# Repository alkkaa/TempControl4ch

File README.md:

# 4 Channel Temperature Control

## MAX31856 Precision Thermocouple to Digital Converter with Linearization

>### General Description
<p>
The MAX31856 performs cold-junction compensation and digitizes the signal from any type of thermocouple. 
The output data is formatted in degrees Celsius.<br>This converter resolves temperatures to 0.0078125°C, allows readings as high as +1800°C and as low as -210°C (depending on thermocouple type), and exhibits thermocouple voltage measurement accuracy of ±0.15%.
<br>The thermocouple inputs are protected against overvoltage conditions up to ±45V.<br>A lookup table (LUT) stores linearity correction data for several types of thermocouple (K, J, N, R, S, T, E, and B)
Line frequency filtering of 50Hz and 60Hz is included, as is thermocouple fault detection.<br>A SPI-compatible interface allows selection of thermocouple type and setup of the conversion and fault detection processes.
<p>

>### Benefits and Features
<ul>
    <li>Provides High-Accuracy Thermocouple Temperature Readings
        <ul>
        <li>Includes Automatic Linearization Correction for 8 Thermocouple Types</li>
        <li>±0.15% (max, -20°C to +85°C) Thermocouple Full-Scale and Linearity Error</li>
        <li>19-Bit, 0.0078125°C Thermocouple Temperature Resolution</li>
        </ul>
    </li>
    <li>Internal Cold-Junction Compensation Minimizes System Components
        <ul>
        <li>±0.7°C (max, -20°C to +85°C) Cold-Junction Accuracy </li>
        </ul>
    </li>
    <li>±45V Input Protection Provides Robust System Performance</li>
    <li>Simplifies System Fault Management and Troubleshooting
        <ul>
        <li>Detects Open Thermocouples</li>
        <li>Over- and Undertemperature Fault Detection</li>
        </ul>
    </li>
    <li>50Hz/60Hz Noise Rejection Filtering Improves System Performance
    </li>
    <li>14-Pin TSSOP Package
    </li>
</ul>

>### Images

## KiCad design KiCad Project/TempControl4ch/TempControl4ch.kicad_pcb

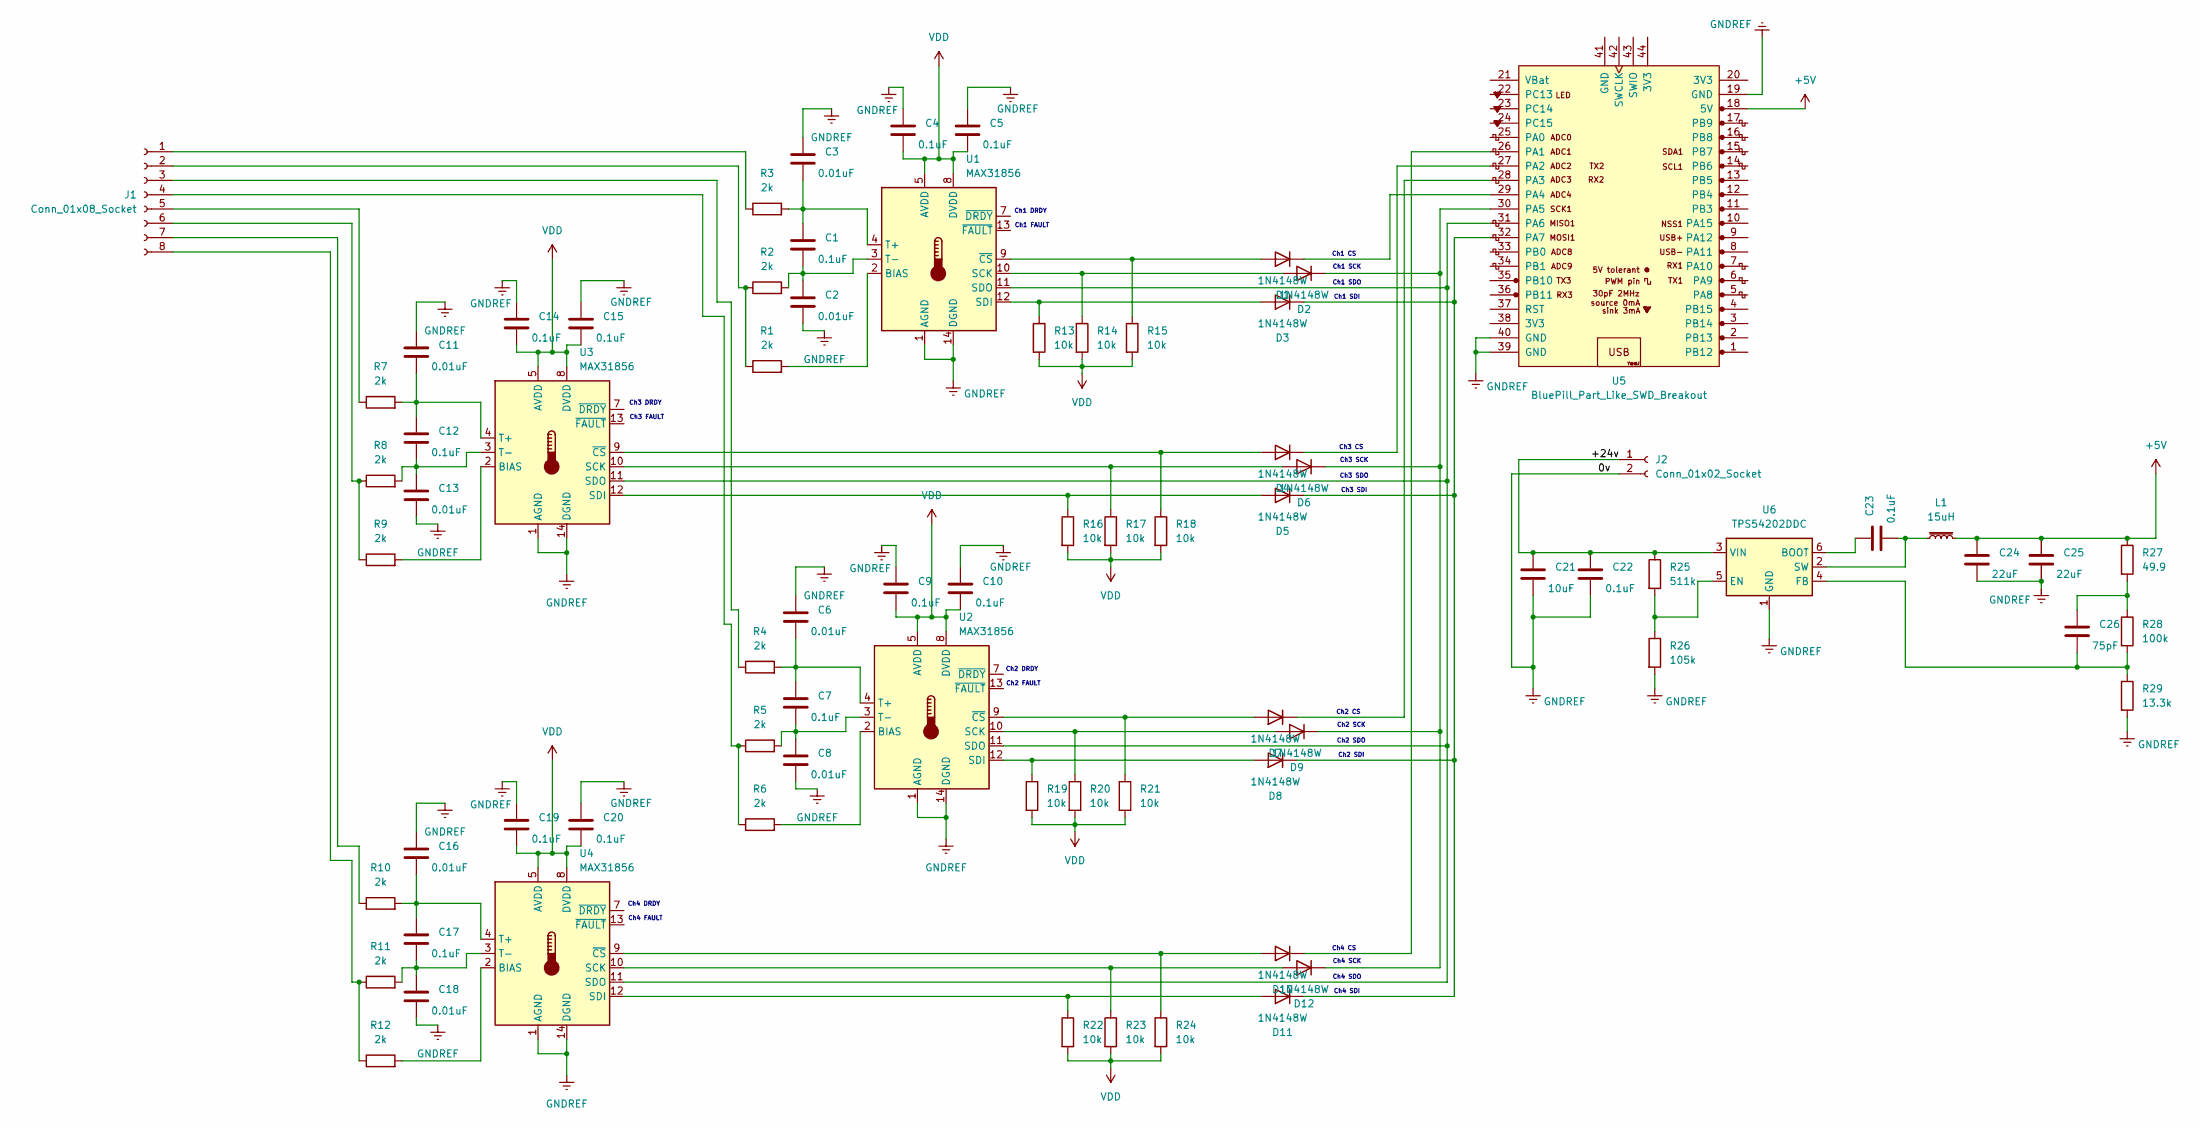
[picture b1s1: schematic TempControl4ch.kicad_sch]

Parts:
C1, C4, C5, C7, C9, C10, C12, C14, C15, C17, C19, C20, C22, C23: 0.1uF; C_1206_3216Metric_Pad1.33x1.80mm_HandSolder
C2, C3, C6, C8, C11, C13, C16, C18: 0.01uF; C_1206_3216Metric_Pad1.33x1.80mm_HandSolder
C21: 10uF; C_1206_3216Metric_Pad1.33x1.80mm_HandSolder
C24, C25: 22uF; C_1206_3216Metric_Pad1.33x1.80mm_HandSolder
C26: 75pF; C_1206_3216Metric_Pad1.33x1.80mm_HandSolder
D1, D2, D3, D4, D5, D6, D7, D8, D9, D10, D11, D12: 1N4148W; D_SOD-123
J1: Conn_01x08_Socket; PhoenixContact_MCV_1,5_8-G-3.81_1x08_P3.81mm_Vertical
J2: Conn_01x02_Socket; PhoenixContact_MCV_1,5_2-G-3.5_1x02_P3.50mm_Vertical
L1: 15uH; L_Sumida_CDMC6D28_7.25x6.5mm
R1, R2, R3, R4, R5, R6, R7, R8, R9, R10, R11, R12: 2k; R_1206_3216Metric_Pad1.30x1.75mm_HandSolder
R13, R14, R15, R16, R17, R18, R19, R20, R21, R22, R23, R24: 10k; R_1206_3216Metric_Pad1.30x1.75mm_HandSolder
R25: 511k; R_1206_3216Metric_Pad1.30x1.75mm_HandSolder
R26: 105k; R_1206_3216Metric_Pad1.30x1.75mm_HandSolder
R27: 49.9; R_1206_3216Metric_Pad1.30x1.75mm_HandSolder
R28: 100k; R_1206_3216Metric_Pad1.30x1.75mm_HandSolder
R29: 13.3k; R_1206_3216Metric_Pad1.30x1.75mm_HandSolder
U1, U2, U3, U4: MAX31856; TSSOP-14_4.4x5mm_P0.65mm
U5: BluePill_Part_Like_SWD_Breakout; BluePill_SWD_1
U6: TPS54202DDC; SOT-23-6

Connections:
+5V: C24.1, C25.1, L1.2, R27.1, U5.18 (5V)
/+24v: C21.1, C22.1, J2.1, R25.1, U6.3 (VIN)
GNDREF: C2.2, C3.1, C4.1, C5.1, C6.1, C8.2, C9.1, C10.1, C11.1, C13.2, C14.1, C15.1, C16.1, C18.2, C19.1, C20.1, C21.2, C22.2, C24.2, C25.2, J2.2, R26.2, R29.2, U1.1 (AGND), U1.14 (DGND), U2.1 (AGND), U2.14 (DGND), U3.1 (AGND), U3.14 (DGND), U4.1 (AGND), U4.14 (DGND), U5.19 (GND), U5.39 (GND), U5.40 (GND), U6.1 (GND)
unnamed: C26.1, R27.2, R28.1
unnamed: D1.2 (A), R15.1, U1.9 (~CS)
unnamed: D1.1 (K), U5.29 (PA4)
unnamed: D2.2 (A), R14.1, U1.10 (SCK)
unnamed: D3.2 (A), R13.1, U1.12 (SDI)
unnamed: D4.2 (A), R18.1, U3.9 (~CS)
unnamed: D4.1 (K), U5.27 (PA2)
unnamed: D5.2 (A), R16.1, U3.12 (SDI)
unnamed: D6.2 (A), R17.1, U3.10 (SCK)
unnamed: D7.2 (A), R21.1, U2.9 (~CS)
unnamed: D7.1 (K), U5.28 (PA3)
unnamed: D8.2 (A), R19.1, U2.12 (SDI)
unnamed: D9.2 (A), R20.1, U2.10 (SCK)
unnamed: D10.2 (A), R24.1, U4.9 (~CS)
unnamed: D10.1 (K), U5.26 (PA1)
unnamed: D11.2 (A), R22.1, U4.12 (SDI)
unnamed: D3.1 (K), D5.1 (K), D8.1 (K), D11.1 (K), U5.32 (PA7)
unnamed: D12.2 (A), R23.1, U4.10 (SCK)
unnamed: D2.1 (K), D6.1 (K), D9.1 (K), D12.1 (K), U5.30 (PA5)
unnamed: J1.1, R3.1
unnamed: J1.2, R1.1, R2.1
unnamed: J1.3, R4.1
unnamed: J1.4, R5.1, R6.1
unnamed: J1.5, R7.1
unnamed: J1.6, R8.1, R9.1
unnamed: J1.7, R10.1
unnamed: J1.8, R11.1, R12.1
unnamed: R1.2, U1.2 (BIAS)
unnamed: U1.11 (SDO), U2.11 (SDO), U3.11 (SDO), U4.11 (SDO), U5.31 (PA6)
unnamed: C1.1, C3.2, R3.2, U1.4 (T+)
unnamed: C1.2, C2.1, R2.2, U1.3 (T-)
unnamed: R6.2, U2.2 (BIAS)
unnamed: C6.2, C7.1, R4.2, U2.4 (T+)
unnamed: C7.2, C8.1, R5.2, U2.3 (T-)
unnamed: R9.2, U3.2 (BIAS)
unnamed: C11.2, C12.1, R7.2, U3.4 (T+)
unnamed: C12.2, C13.1, R8.2, U3.3 (T-)
unnamed: R12.2, U4.2 (BIAS)
unnamed: C16.2, C17.1, R10.2, U4.4 (T+)
unnamed: C17.2, C18.1, R11.2, U4.3 (T-)
unnamed: C23.1, U6.6 (BOOT)
unnamed: R25.2, R26.1, U6.5 (EN)
unnamed: C26.2, R28.2, R29.1, U6.4 (FB)
unnamed: C23.2, L1.1, U6.2 (SW)
VDD: C4.2, C5.2, C9.2, C10.2, C14.2, C15.2, C19.2, C20.2, R13.2, R14.2, R15.2, R16.2, R17.2, R18.2, R19.2, R20.2, R21.2, R22.2, R23.2, R24.2, U1.5 (AVDD), U1.8 (DVDD), U2.5 (AVDD), U2.8 (DVDD), U3.5 (AVDD), U3.8 (DVDD), U4.5 (AVDD), U4.8 (DVDD)

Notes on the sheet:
Ch1 SCK
Ch2 SCK
Ch2 DRDY
Ch4 SDI
Ch4 FAULT
Ch3 FAULT
Ch3 SDO
Ch4 CS
Ch4 SCK
Ch1 FAULT
Ch2 SDO
Ch1 SDI
Ch2 CS
Ch2 FAULT
Ch1 DRDY
Ch1 CS
Ch4 DRDY
Ch3 SCK
Ch4 SDO
Ch1 SDO
Ch3 SDI
Ch3 CS
Ch2 SDI
Ch3 DRDY

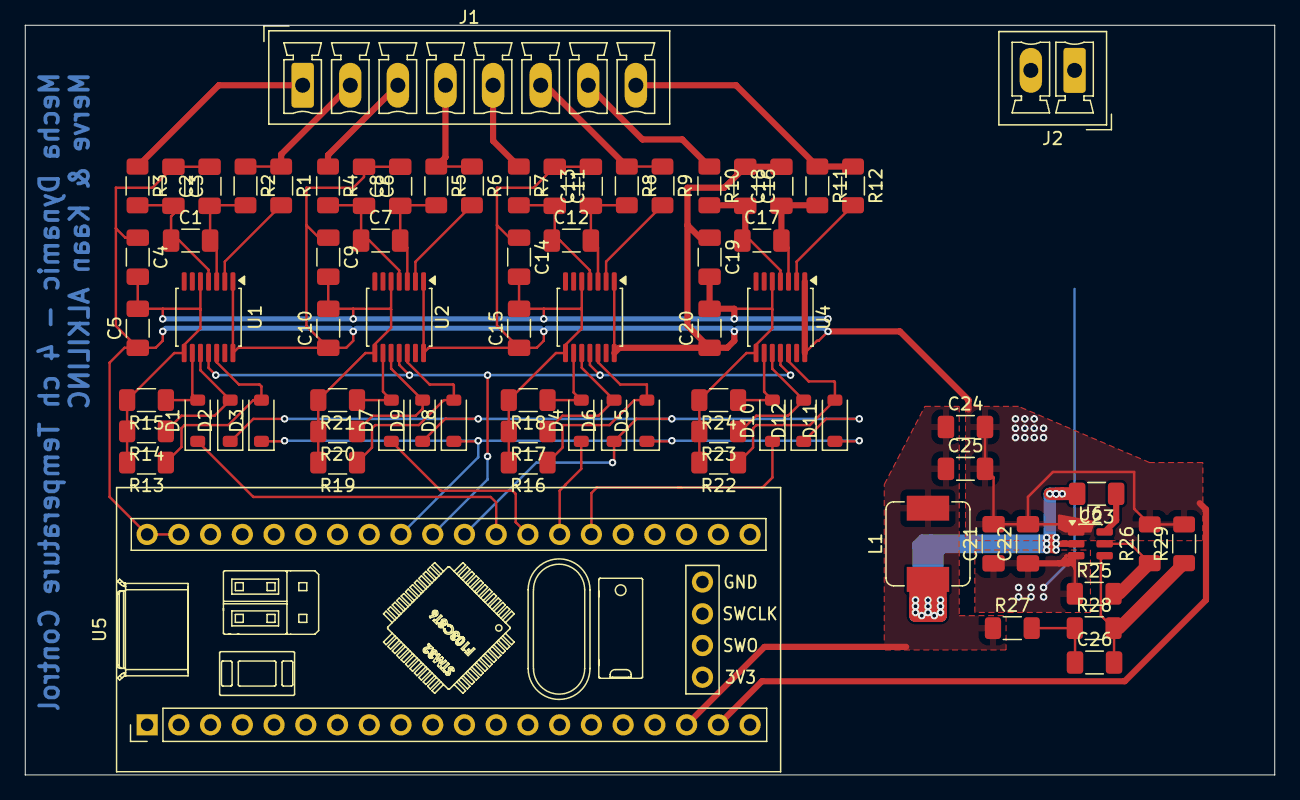
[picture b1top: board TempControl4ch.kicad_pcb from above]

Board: 2 copper layers, 100.0 x 60.0 mm, 76 parts (0 on the bottom side), 48 nets.

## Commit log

2025-12-24 24.12.2025 change README.md
2025-12-24 added Images
2025-12-24 change readme.md
2025-12-26 added SPI connections and update schematic & pcb
2025-12-27 update schematic & pcb, all pcb wiring is completed
2025-12-27 3d view updated
2025-12-28 added 24v to 5v converter schematic
2025-12-28 update supply circuit pcb design
2025-12-29 update pcb design
